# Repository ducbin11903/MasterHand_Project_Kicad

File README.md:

<h1 align="center">Motor Control Board</h1>

<p align="center" width="100%">
  
</p>

***

<p align="center">
  
&nbsp; &nbsp; &nbsp; &nbsp;
  
</p>

***

## SPECIFICATIONS

| Parameter | Value | 
| --- | --- |
| Dimensions | 79.0 × 65.81 mm |

***

## DIRECTORY STRUCTURE

    .
    ├─ Computations       # Misc calculations
    ├─ HTML               # HTML files for generated webpage
    ├─ Images             # Pictures and renders
    │
    ├─ kibot_resources    # External resources for KiBot
    │  ├─ colors          # Color theme for KiCad
    │  ├─ fonts           # Fonts used in the project
    │  ├─ scripts         # External scripts used with KiBot
    │  └─ templates       # Templates for KiBot generated reports
    │
    ├─ kibot_yaml         # KiBot YAML config files
    ├─ KiRI               # KiRI (PCB diff viewer) files
    │
    ├─ lib                # KiCad footprint and symbol libraries
    │  ├─ 3d_models       # Component 3D models
    │  ├─ lib_fp          # Footprint libraries
    │  └─ lib_sym         # Symbol libraries
    │
    ├─ Logos              # Logos
    │
    ├─ Manufacturing      # Assembly and fabrication documents
    │  ├─ Assembly        # Assembly documents (BoM, pos, notes)
    │  │
    │  └─ Fabrication     # Fabrication documents (ZIP, notes)
    │     ├─ Drill Tables # CSV drill tables
    │     └─ Gerbers      # Gerbers
    │
    ├─ Report             # Reports for ERC/DRC
    ├─ Schematic          # PDF of schematic
    ├─ Templates          # Title block templates
    ├─ Testing
    │  └─ Testpoints      # Testpoints tables      
    │
    └─ Variants           # Outputs for assembly variants

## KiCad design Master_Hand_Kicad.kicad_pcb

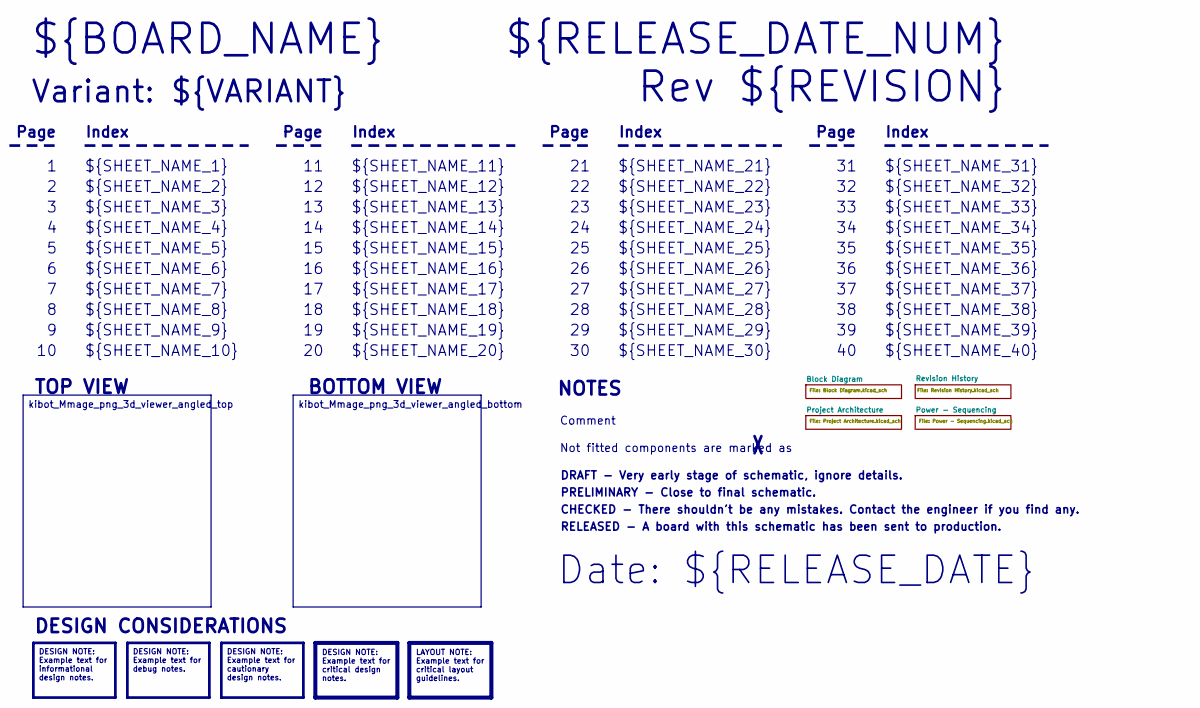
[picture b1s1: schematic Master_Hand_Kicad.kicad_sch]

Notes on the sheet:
Variant: ${VARIANT}
RELEASED - A board with this schematic has been sent to production.
${SHEET_NAME_24}
Index
Page
PRELIMINARY - Close to final schematic.
${SHEET_NAME_22}
DRAFT - Very early stage of schematic, ignore details.
${SHEET_NAME_12}
${SHEET_NAME_8}
${SHEET_NAME_2}
${SHEET_NAME_5}
${SHEET_NAME_20}
${SHEET_NAME_23}
${RELEASE_DATE_NUM}
${SHEET_NAME_35}
Not fitted components are marked as
${SHEET_NAME_11}
${SHEET_NAME_6}
${SHEET_NAME_37}
${SHEET_NAME_26}
${SHEET_NAME_36}
Rev ${REVISION}
${SHEET_NAME_15}
CHECKED - There shouldn't be any mistakes. Contact the engineer if you find any.
BOTTOM VIEW
${SHEET_NAME_14}
${SHEET_NAME_21}
${SHEET_NAME_17}
${SHEET_NAME_18}
Date: ${RELEASE_DATE}
${SHEET_NAME_7}
${SHEET_NAME_31}
${BOARD_NAME}
NOTES
${SHEET_NAME_40}
${SHEET_NAME_39}
${SHEET_NAME_32}
${SHEET_NAME_1}
${SHEET_NAME_9}

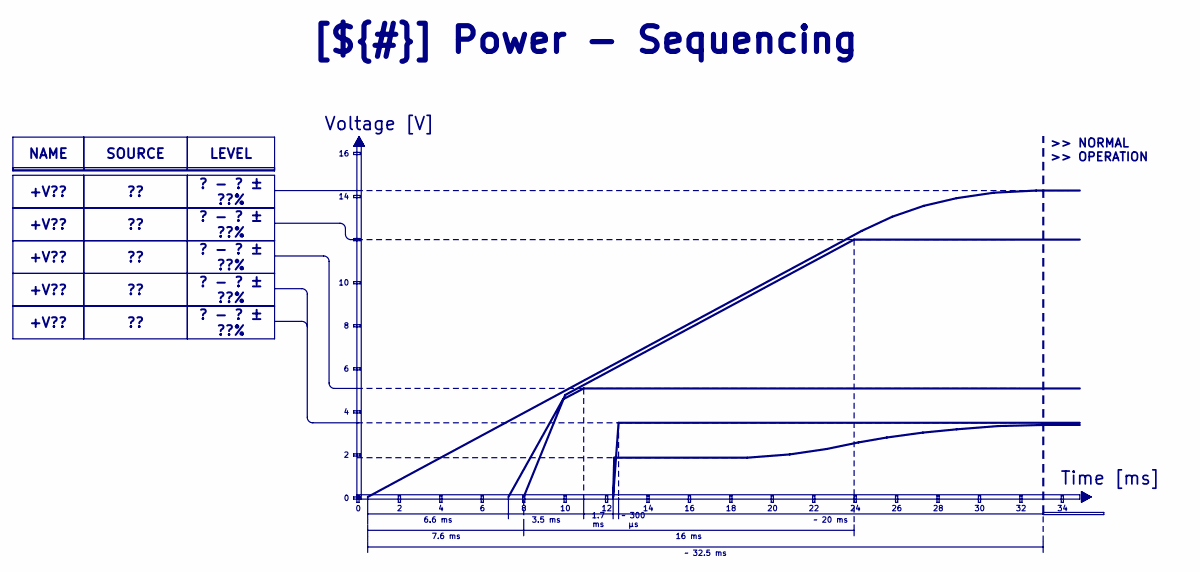
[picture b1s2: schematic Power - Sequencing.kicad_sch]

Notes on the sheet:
Voltage [V]
>> NORMAL >> OPERATION
Time [ms]
3.5 ms
7.6 ms
? - ? ± ??%
~ 300 μs
1.7 ms
16 ms
+V??
LEVEL
NAME
~ 20 ms
SOURCE
[${#}] ${TITLE}
6.6 ms
~ 32.5 ms

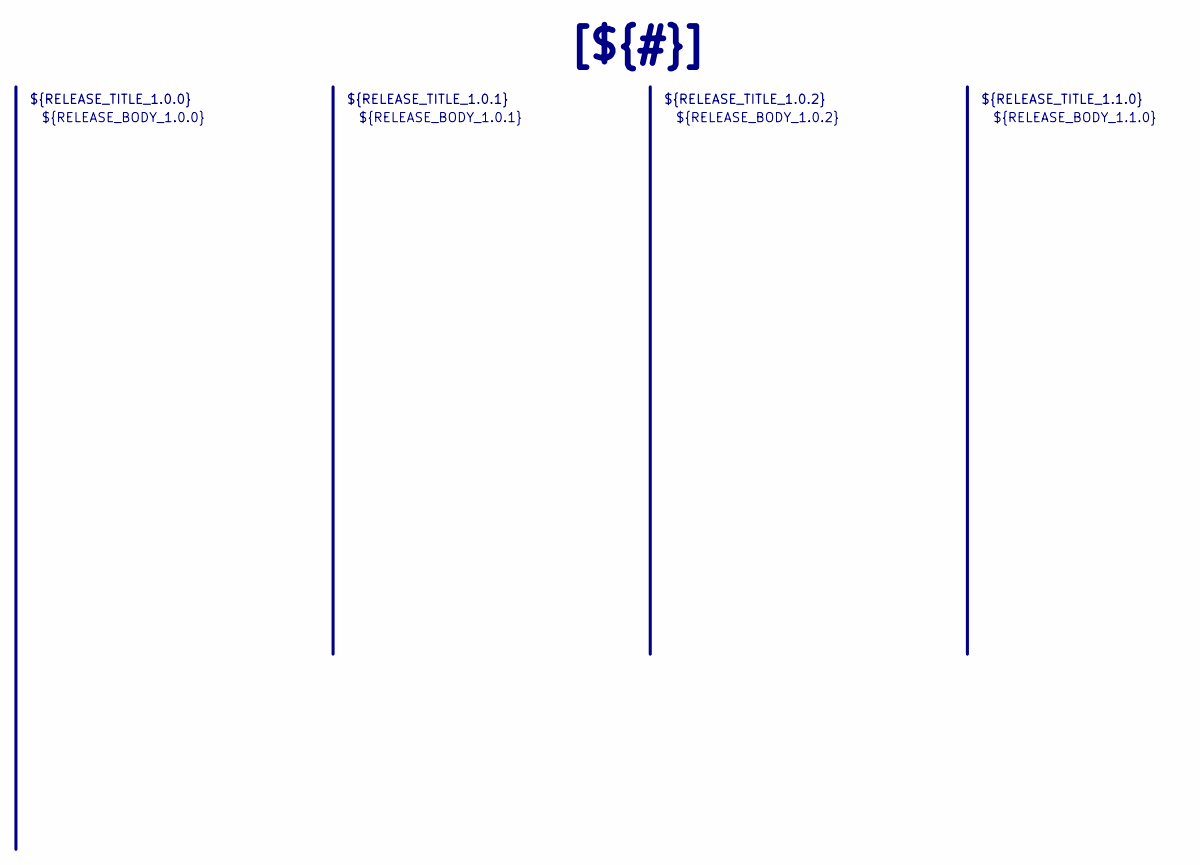
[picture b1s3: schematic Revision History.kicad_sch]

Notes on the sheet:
${RELEASE_BODY_1.1.0}
[${#}] ${TITLE}
${RELEASE_BODY_1.0.0}
${RELEASE_TITLE_1.0.2}
${RELEASE_BODY_1.0.2}
${RELEASE_BODY_1.0.1}
${RELEASE_TITLE_1.0.0}
${RELEASE_TITLE_1.0.1}
${RELEASE_TITLE_1.1.0}

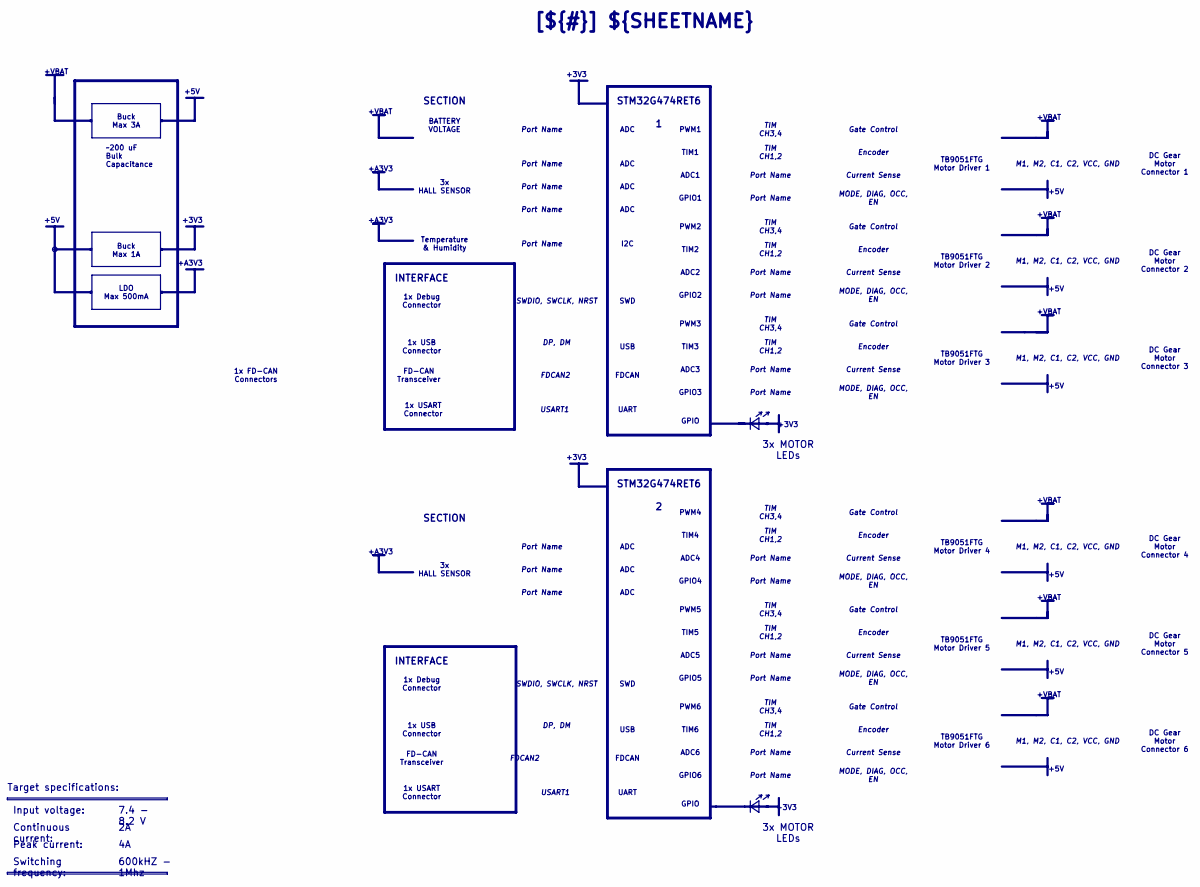
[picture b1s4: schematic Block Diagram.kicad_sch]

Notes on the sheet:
+5V
+A3V3
+VBAT
+3V3
+3V3
+VBAT
SWDIO, SWCLK, NRST
TIM CH3,4
I2C
MODE, DIAG, OCC, EN
Current Sense
TB9051FTG Motor Driver 6
7.4 - 8.2 V
TIM CH1,2
USB
ADC
M1, M2, C1, C2, VCC, GND
Temperature & Humidity
TIM6
1x FD-CAN Connectors
1x USART Connector
TIM CH3,4
600kHZ - 1Mhz
Port Name
STM32G474RET6
GPIO5
TIM1
TIM2
Gate Control
INTERFACE
SWD
DC Gear Motor Connector 3
3x HALL SENSOR
DC Gear Motor Connector 2
Peak current:
FDCAN
Encoder
PWM3
USART1
TB9051FTG Motor Driver 2

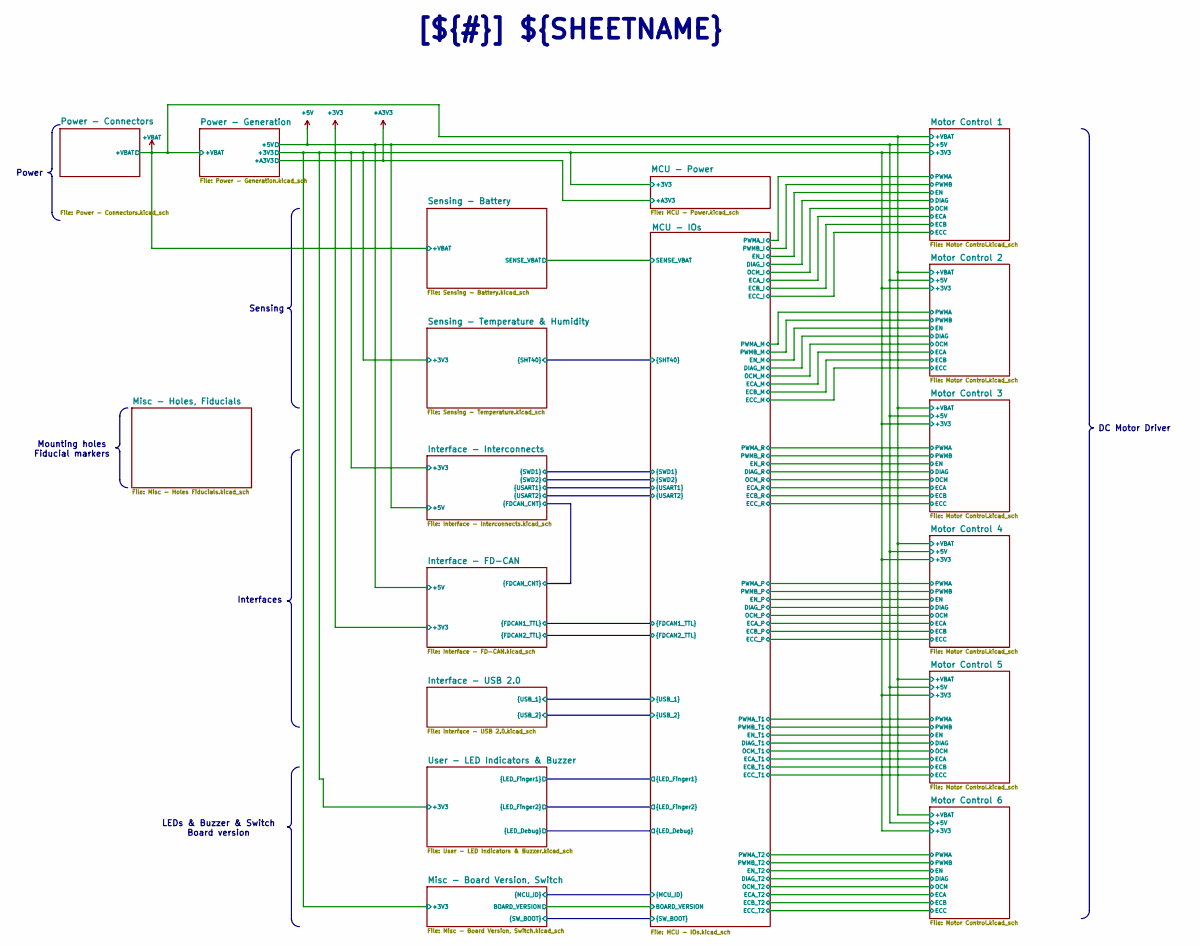
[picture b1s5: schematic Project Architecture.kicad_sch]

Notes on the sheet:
Mounting holes Fiducial markers
Interfaces
Power
LEDs & Buzzer & Switch Board version
[${#}] ${SHEETNAME}
Sensing
DC Motor Driver

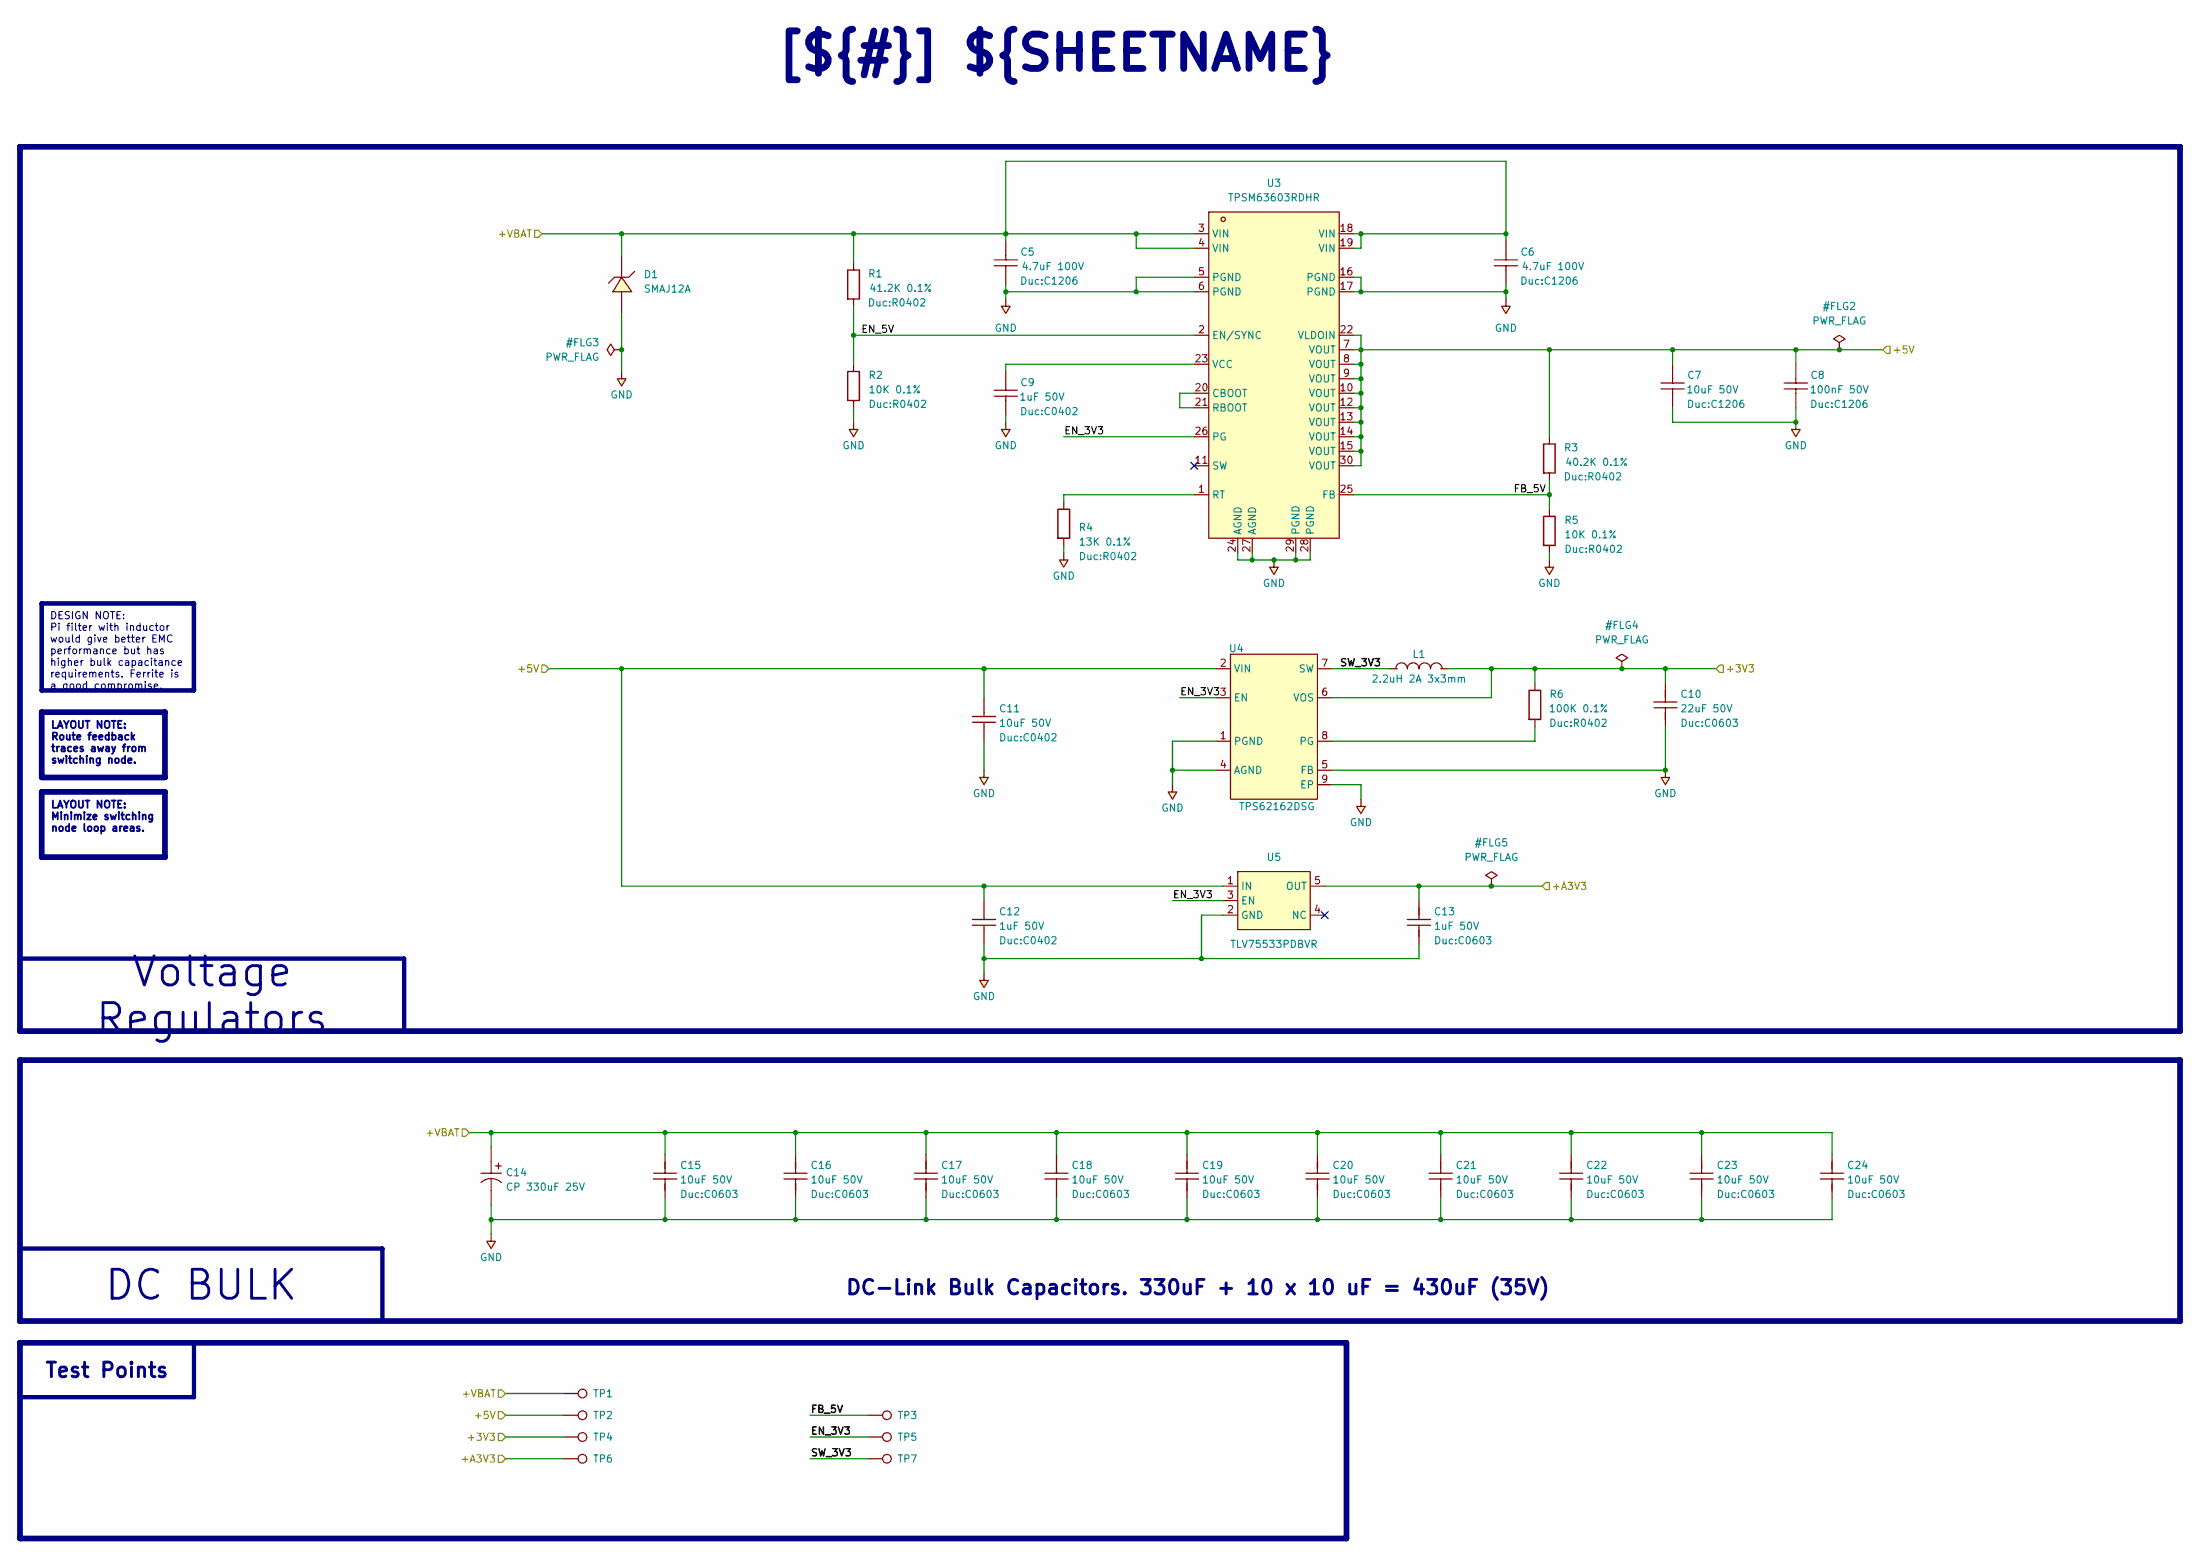
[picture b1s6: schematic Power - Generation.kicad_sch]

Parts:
C5, C6: 4.7uF 100V; C1206; MPN CC1206KKX7R9BB475; LCSC Part C132170
C7: 10uF 50V; C1206; MPN CC1206KKX7R9BB475; LCSC Part C132170
C8: 100nF 50V; C1206; MPN CC1206KKX7R9BB475; LCSC Part C132170
C9, C12: 1uF 50V; C0402; MPN CC0402KRX5R7BB105; LCSC Part C325464
C10: 22uF 50V; C0603; MPN CAP CER 0603; LCSC Part C14663
C11: 10uF 50V; C0402; MPN CC0402KRX5R7BB105; LCSC Part C325464
C13: 1uF 50V; C0603; MPN CAP CER 0603; LCSC Part C14663
C14: SM337M025E0800; CAP-SMD_BD6.3-L6.6-W6.6-FD-1; MPN SM337M025E0800; LCSC Part C44606382
C15, C16, C17, C18, C19, C20, C21, C22, C23, C24: 10uF 50V; C0603; MPN CAP CER 0603; LCSC Part C14663
D1: SMAJ12A; SMA_L4.3-W2.6-LS5.2-RD; MPN SMAJ12A; LCSC Part C148213
L1: ANR3015T2R2M; IND-SMD_L3.0-W3.0_SMNR3015; MPN ANR3015T2R2M; LCSC Part C6364793
R1: 41.2K 0.1%; R0402; MPN RT0402FRE07100KL; LCSC Part C728576
R2, R5: 10K 0.1%; R0402; MPN RT0402FRE07100KL; LCSC Part C728576
R3: 40.2K 0.1%; R0402; MPN RT0402FRE07100KL; LCSC Part C728576
R4: 13K 0.1%; R0402; MPN RT0402FRE07100KL; LCSC Part C728576
R6: 100K 0.1%; R0402; MPN RT0402FRE07100KL; LCSC Part C728576
TP1, TP2, TP3, TP4, TP5, TP6, TP7: TestPoint_Pad_D0.5mm
U3: TPSM63603RDHR; QFN-30_L6.0-W4.0-P0.50_TLVM13630RDHR; MPN TPSM63603RDHR; LCSC Part C5219327
U4: TPS62162DSG; WSON-8_L2.0-W2.0-P0.50-TL-EP; MPN TPS62162DSGR; LCSC Part C40256
U5: TLV75533PDBVR; SOT-23-5_L3.0-W1.7-P0.95-LS2.8-BR; MPN TLV75533PDBVR; LCSC Part C404027

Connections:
+3V3: C10.2, L1.2, R6.2, TP4.1, U4.6 (VOS); also elsewhere on the board
+5V: C7.2, C8.2, C11.2, C12.2, R3.2, TP2.1, U3.7 (VOUT), U3.8 (VOUT), U3.9 (VOUT), U3.10 (VOUT), U3.12 (VOUT), U3.13 (VOUT), U3.14 (VOUT), U3.15 (VOUT), U3.22 (VLDOIN), U3.30 (VOUT), U4.2 (VIN), U5.1 (IN); also elsewhere on the board
+A3V3: C13.2, TP6.1, U5.5 (OUT); also elsewhere on the board
+VBAT: C5.1, C6.2, C14.1, C15.1, C16.1, C17.1, C18.1, C19.1, C20.1, C21.1, C22.1, C23.1, C24.1, D1.1 (C), R1.2, TP1.1, U3.3 (VIN), U3.4 (VIN), U3.18 (VIN), U3.19 (VIN); also elsewhere on the board
/Project Architecture/Power - Generation/EN_3V3: TP5.1, U3.26 (PG), U4.3 (EN), U5.3 (EN)
/Project Architecture/Power - Generation/EN_5V: R1.1, R2.2, U3.2 (EN/SYNC)
/Project Architecture/Power - Generation/FB_5V: R3.1, R5.2, TP3.1, U3.25 (FB)
/Project Architecture/Power - Generation/SW_3V3: L1.1, TP7.1, U4.7 (SW)
GND: C5.2, C6.1, C7.1, C8.1, C9.2, C10.1, C11.1, C12.1, C13.1, C14.2, C15.2, C16.2, C17.2, C18.2, C19.2, C20.2, C21.2, C22.2, C23.2, C24.2, D1.2 (A), R2.1, R4.1, R5.1, U3.5 (PGND), U3.6 (PGND), U3.16 (PGND), U3.17 (PGND), U3.24 (AGND), U3.27 (AGND), U3.28 (PGND), U3.29 (PGND), U4.1 (PGND), U4.4 (AGND), U4.5 (FB), U4.9 (EP), U5.2 (GND); also elsewhere on the board
unnamed: U3.20 (CBOOT), U3.21 (RBOOT)
unnamed: R4.2, U3.1 (RT)
unnamed: C9.1, U3.23 (VCC)
unnamed: R6.1, U4.8 (PG)

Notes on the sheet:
DC BULK
Voltage Regulators
[${#}] ${SHEETNAME}
LAYOUT NOTE: Minimize switching node loop areas.
DESIGN NOTE: Pi filter with inductor would give better EMC performance but has higher bulk capacitance requirements. Ferrite is a good compromise.
DC-Link Bulk Capacitors. 330uF + 10 x 10 uF = 430uF (35V)
LAYOUT NOTE: Route feedback traces away from switching node.
Test Points

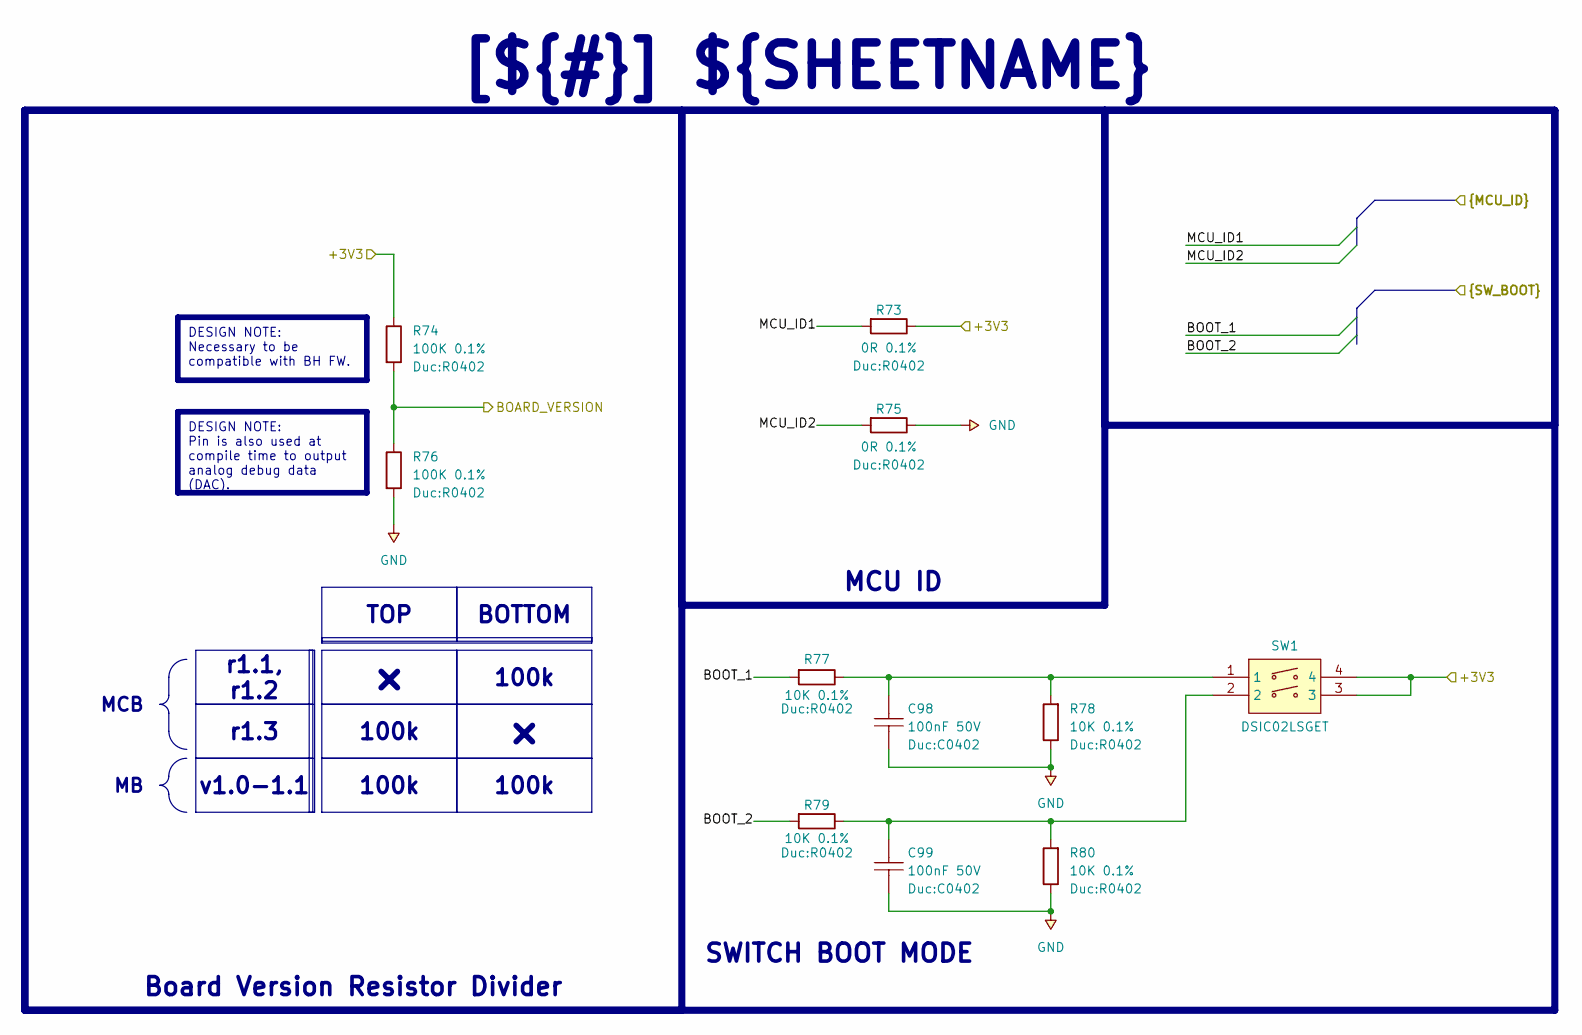
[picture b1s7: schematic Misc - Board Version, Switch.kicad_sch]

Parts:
C98, C99: 100nF 50V; C0402; MPN CC0402KRX5R7BB105; LCSC Part C325464
R73, R75: 0R 0.1%; R0402; MPN RT0402FRE07100KL; LCSC Part C728576
R74, R76: 100K 0.1%; R0402; MPN RT0402FRE07100KL; LCSC Part C728576
R77, R78, R79, R80: 10K 0.1%; R0402; MPN RT0402FRE07100KL; LCSC Part C728576
SW1: DSIC02LSGET; SW-SMD_DSIC02LSGET; MPN DSIC02LSGET; LCSC Part C3293152

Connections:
+3V3: R73.2, R74.2, SW1.3, SW1.4; also elsewhere on the board
/Project Architecture/MCU - IOs/BOARD_VERSION: R74.1, R76.2; also elsewhere on the board
/Project Architecture/MCU - IOs/BOOT_1: R77.1; also elsewhere on the board
/Project Architecture/MCU - IOs/BOOT_2: R79.1; also elsewhere on the board
/Project Architecture/MCU - IOs/MCU_ID1: R73.1; also elsewhere on the board
/Project Architecture/MCU - IOs/MCU_ID2: R75.1; also elsewhere on the board
GND: C98.1, C99.1, R75.2, R76.1, R78.2, R80.2; also elsewhere on the board
unnamed: C98.2, R77.2, R78.1, SW1.1
unnamed: C99.2, R79.2, R80.1, SW1.2

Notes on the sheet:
DESIGN NOTE: Necessary to be compatible with BH FW.
r1.3
MCU ID
TOP
BOTTOM
r1.1, r1.2
DESIGN NOTE: Pin is also used at compile time to output analog debug data (DAC).
Board Version Resistor Divider
100k
MCB
SWITCH BOOT MODE
[${#}] ${SHEETNAME}
v1.0-1.1

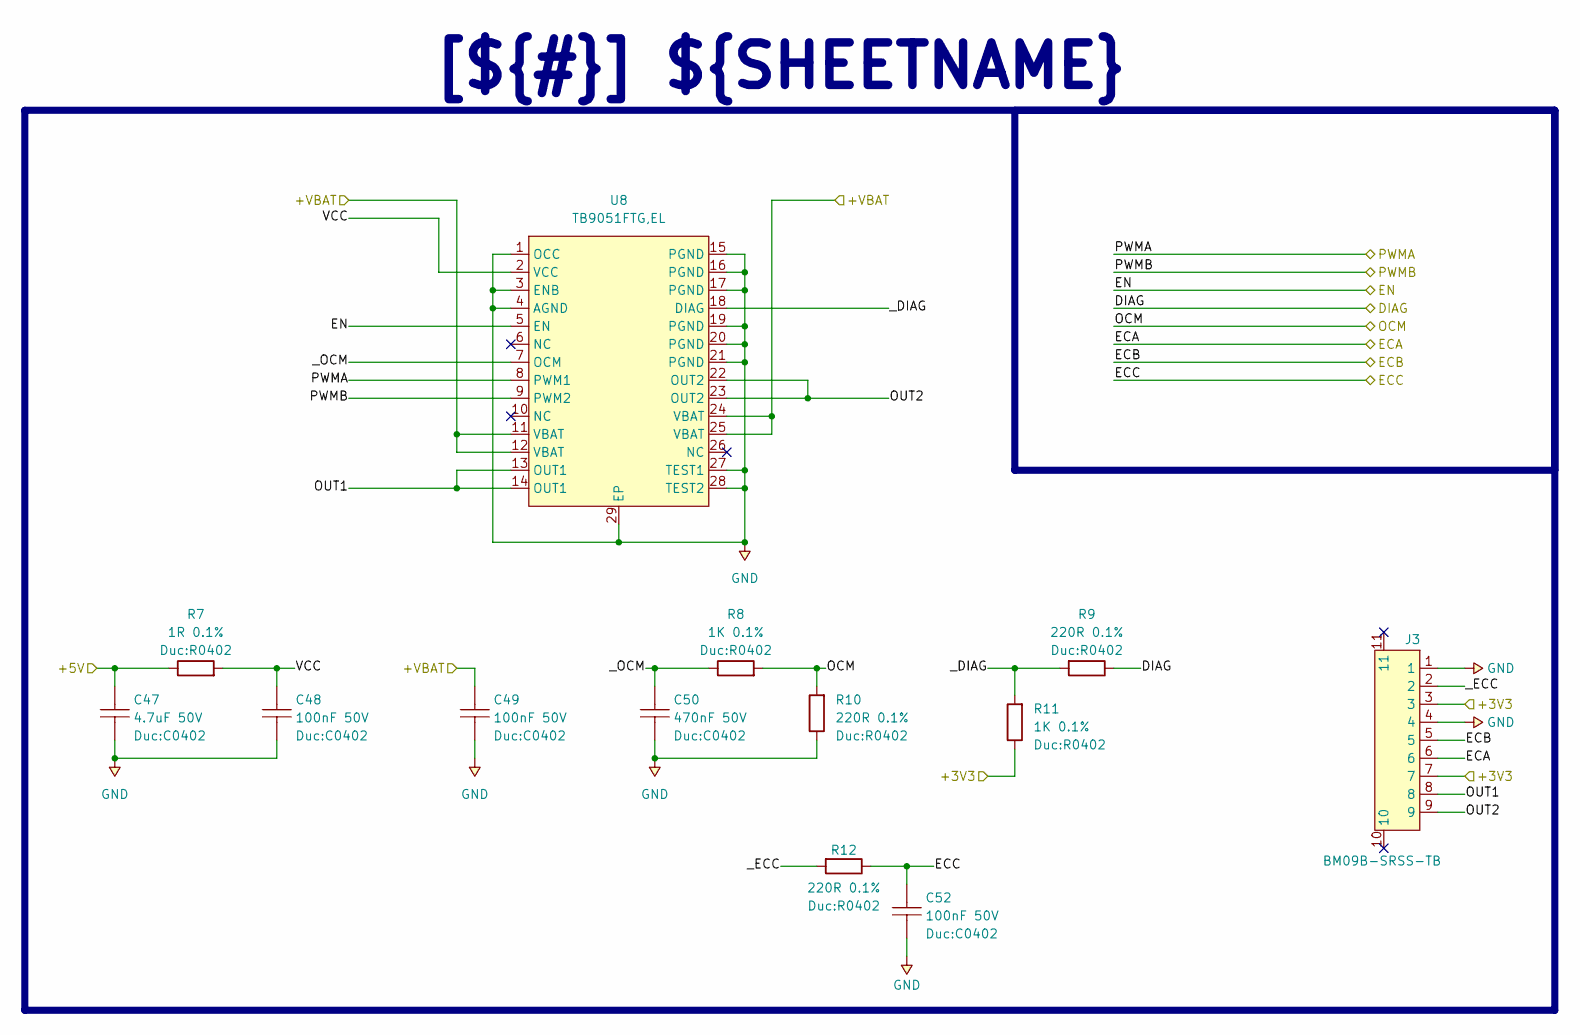
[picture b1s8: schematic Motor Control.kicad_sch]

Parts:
C47: 4.7uF 50V; C0402; MPN CC0402KRX5R7BB105; LCSC Part C325464
C48, C49, C52: 100nF 50V; C0402; MPN CC0402KRX5R7BB105; LCSC Part C325464
C50: 470nF 50V; C0402; MPN CC0402KRX5R7BB105; LCSC Part C325464
J3: BM09B-SRSS-TB; CONN-SMD_9P-P1.00_BM09B-SRSS-TB; MPN BM09B-SRSS-TB(LF)(SN); LCSC Part C160395
R7: 1R 0.1%; R0402; MPN RT0402FRE07100KL; LCSC Part C728576
R8, R11: 1K 0.1%; R0402; MPN RT0402FRE07100KL; LCSC Part C728576
R9, R10, R12: 220R 0.1%; R0402; MPN RT0402FRE07100KL; LCSC Part C728576
U8: TB9051FTG,EL; UQFN-28_L6.0-W6.0-P0.65-BL-EP4.0; MPN TB9051FTG,EL; LCSC Part C2150635

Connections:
+3V3: J3.3, J3.7, R11.2; also elsewhere on the board
+5V: C47.2, R7.2; also elsewhere on the board
+VBAT: C49.2, U8.11 (VBAT), U8.12 (VBAT), U8.24 (VBAT), U8.25 (VBAT); also elsewhere on the board
/Project Architecture/MCU - IOs/DIAG_I: R9.2; also elsewhere on the board
/Project Architecture/MCU - IOs/ECA_I: J3.6; also elsewhere on the board
/Project Architecture/MCU - IOs/ECB_I: J3.5; also elsewhere on the board
/Project Architecture/MCU - IOs/ECC_I: C52.2, R12.2; also elsewhere on the board
/Project Architecture/MCU - IOs/EN_I: U8.5 (EN); also elsewhere on the board
/Project Architecture/MCU - IOs/OCM_I: R8.1, R10.1; also elsewhere on the board
/Project Architecture/MCU - IOs/PWMA_I: U8.8 (PWM1); also elsewhere on the board
/Project Architecture/MCU - IOs/PWMB_I: U8.9 (PWM2); also elsewhere on the board
/Project Architecture/Motor Control 1/OUT1: J3.8, U8.13 (OUT1), U8.14 (OUT1)
/Project Architecture/Motor Control 1/OUT2: J3.9, U8.22 (OUT2), U8.23 (OUT2)
/Project Architecture/Motor Control 1/VCC: C48.2, R7.1, U8.2 (VCC)
/Project Architecture/Motor Control 1/_DIAG: R9.1, R11.1, U8.18 (DIAG)
/Project Architecture/Motor Control 1/_ECC: J3.2, R12.1
/Project Architecture/Motor Control 1/_OCM: C50.2, R8.2, U8.7 (OCM)
GND: C47.1, C48.1, C49.1, C50.1, C52.1, J3.1, J3.4, R10.2, U8.1 (OCC), U8.3 (ENB), U8.4 (AGND), U8.15 (PGND), U8.16 (PGND), U8.17 (PGND), U8.19 (PGND), U8.20 (PGND), U8.21 (PGND), U8.27 (TEST1), U8.28 (TEST2), U8.29 (EP); also elsewhere on the board

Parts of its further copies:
C53, C59, C65, C71, C77: 4.7uF 50V; C0402; MPN CC0402KRX5R7BB105; LCSC Part C325464
C54, C55, C58, C60, C61, C64, C66, C67, C70, C72, C73, C76, C78, C79, C82: 100nF 50V; C0402; MPN CC0402KRX5R7BB105; LCSC Part C325464
C56, C62, C68, C74, C80: 470nF 50V; C0402; MPN CC0402KRX5R7BB105; LCSC Part C325464
J4, J5, J6, J7, J8: BM09B-SRSS-TB; CONN-SMD_9P-P1.00_BM09B-SRSS-TB; MPN BM09B-SRSS-TB(LF)(SN); LCSC Part C160395
R13, R19, R25, R31, R37: 1R 0.1%; R0402; MPN RT0402FRE07100KL; LCSC Part C728576
R14, R17, R20, R23, R26, R29, R32, R35, R38, R41: 1K 0.1%; R0402; MPN RT0402FRE07100KL; LCSC Part C728576
R15, R16, R18, R21, R22, R24, R27, R28, R30, R33, R34, R36, R39, R40, R42: 220R 0.1%; R0402; MPN RT0402FRE07100KL; LCSC Part C728576
U9, U10, U11, U12, U13: TB9051FTG,EL; UQFN-28_L6.0-W6.0-P0.65-BL-EP4.0; MPN TB9051FTG,EL; LCSC Part C2150635

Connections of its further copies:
+3V3: J4.3, J4.7, J5.3, J5.7, J6.3, J6.7, J7.3, J7.7, J8.3, J8.7, R17.2, R23.2, R29.2, R35.2, R41.2; also elsewhere on the board
+5V: C53.2, C59.2, C65.2, C71.2, C77.2, R13.2, R19.2, R25.2, R31.2, R37.2; also elsewhere on the board
+VBAT: C55.2, C61.2, C67.2, C73.2, C79.2, U9.11 (VBAT), U9.12 (VBAT), U9.24 (VBAT), U9.25 (VBAT), U10.11 (VBAT), U10.12 (VBAT), U10.24 (VBAT), U10.25 (VBAT), U11.11 (VBAT), U11.12 (VBAT), U11.24 (VBAT), U11.25 (VBAT), U12.11 (VBAT), U12.12 (VBAT), U12.24 (VBAT), U12.25 (VBAT), U13.11 (VBAT), U13.12 (VBAT), U13.24 (VBAT), U13.25 (VBAT); also elsewhere on the board
/Project Architecture/MCU - IOs/DIAG_M: R15.2; also elsewhere on the board
/Project Architecture/MCU - IOs/DIAG_P: R27.2; also elsewhere on the board
/Project Architecture/MCU - IOs/DIAG_R: R21.2; also elsewhere on the board
/Project Architecture/MCU - IOs/DIAG_T1: R33.2; also elsewhere on the board
/Project Architecture/MCU - IOs/DIAG_T2: R39.2; also elsewhere on the board
/Project Architecture/MCU - IOs/ECA_M: J4.6; also elsewhere on the board
/Project Architecture/MCU - IOs/ECA_P: J6.6; also elsewhere on the board
/Project Architecture/MCU - IOs/ECA_R: J5.6; also elsewhere on the board
/Project Architecture/MCU - IOs/ECA_T1: J7.6; also elsewhere on the board
/Project Architecture/MCU - IOs/ECA_T2: J8.6; also elsewhere on the board
/Project Architecture/MCU - IOs/ECB_M: J4.5; also elsewhere on the board
/Project Architecture/MCU - IOs/ECB_P: J6.5; also elsewhere on the board
/Project Architecture/MCU - IOs/ECB_R: J5.5; also elsewhere on the board
/Project Architecture/MCU - IOs/ECB_T1: J7.5; also elsewhere on the board
/Project Architecture/MCU - IOs/ECB_T2: J8.5; also elsewhere on the board
/Project Architecture/MCU - IOs/ECC_M: C58.2, R18.2; also elsewhere on the board
/Project Architecture/MCU - IOs/ECC_P: C70.2, R30.2; also elsewhere on the board
/Project Architecture/MCU - IOs/ECC_R: C64.2, R24.2; also elsewhere on the board
/Project Architecture/MCU - IOs/ECC_T1: C76.2, R36.2; also elsewhere on the board
/Project Architecture/MCU - IOs/ECC_T2: C82.2, R42.2; also elsewhere on the board
/Project Architecture/MCU - IOs/EN_M: U9.5 (EN); also elsewhere on the board
/Project Architecture/MCU - IOs/EN_P: U11.5 (EN); also elsewhere on the board
/Project Architecture/MCU - IOs/EN_R: U10.5 (EN); also elsewhere on the board
/Project Architecture/MCU - IOs/EN_T1: U12.5 (EN); also elsewhere on the board
/Project Architecture/MCU - IOs/EN_T2: U13.5 (EN); also elsewhere on the board
/Project Architecture/MCU - IOs/OCM_M: R14.1, R16.1; also elsewhere on the board
/Project Architecture/MCU - IOs/OCM_P: R26.1, R28.1; also elsewhere on the board
/Project Architecture/MCU - IOs/OCM_R: R20.1, R22.1; also elsewhere on the board
/Project Architecture/MCU - IOs/OCM_T1: R32.1, R34.1; also elsewhere on the board
/Project Architecture/MCU - IOs/OCM_T2: R38.1, R40.1; also elsewhere on the board
/Project Architecture/MCU - IOs/PWMA_M: U9.8 (PWM1); also elsewhere on the board
/Project Architecture/MCU - IOs/PWMA_P: U11.8 (PWM1); also elsewhere on the board
/Project Architecture/MCU - IOs/PWMA_R: U10.8 (PWM1); also elsewhere on the board
/Project Architecture/MCU - IOs/PWMA_T1: U12.8 (PWM1); also elsewhere on the board
/Project Architecture/MCU - IOs/PWMA_T2: U13.8 (PWM1); also elsewhere on the board
/Project Architecture/MCU - IOs/PWMB_M: U9.9 (PWM2); also elsewhere on the board
/Project Architecture/MCU - IOs/PWMB_P: U11.9 (PWM2); also elsewhere on the board
/Project Architecture/MCU - IOs/PWMB_R: U10.9 (PWM2); also elsewhere on the board
/Project Architecture/MCU - IOs/PWMB_T1: U12.9 (PWM2); also elsewhere on the board
/Project Architecture/MCU - IOs/PWMB_T2: U13.9 (PWM2); also elsewhere on the board
/Project Architecture/Motor Control 2/OUT1: J4.8, U9.13 (OUT1), U9.14 (OUT1)
/Project Architecture/Motor Control 2/OUT2: J4.9, U9.22 (OUT2), U9.23 (OUT2)
/Project Architecture/Motor Control 2/VCC: C54.2, R13.1, U9.2 (VCC)
/Project Architecture/Motor Control 2/_DIAG: R15.1, R17.1, U9.18 (DIAG)
/Project Architecture/Motor Control 2/_ECC: J4.2, R18.1
/Project Architecture/Motor Control 2/_OCM: C56.2, R14.2, U9.7 (OCM)
/Project Architecture/Motor Control 3/OUT1: J5.8, U10.13 (OUT1), U10.14 (OUT1)
/Project Architecture/Motor Control 3/OUT2: J5.9, U10.22 (OUT2), U10.23 (OUT2)
/Project Architecture/Motor Control 3/VCC: C60.2, R19.1, U10.2 (VCC)
/Project Architecture/Motor Control 3/_DIAG: R21.1, R23.1, U10.18 (DIAG)
/Project Architecture/Motor Control 3/_ECC: J5.2, R24.1
/Project Architecture/Motor Control 3/_OCM: C62.2, R20.2, U10.7 (OCM)
/Project Architecture/Motor Control 4/OUT1: J6.8, U11.13 (OUT1), U11.14 (OUT1)
/Project Architecture/Motor Control 4/OUT2: J6.9, U11.22 (OUT2), U11.23 (OUT2)
/Project Architecture/Motor Control 4/VCC: C66.2, R25.1, U11.2 (VCC)
/Project Architecture/Motor Control 4/_DIAG: R27.1, R29.1, U11.18 (DIAG)
/Project Architecture/Motor Control 4/_ECC: J6.2, R30.1
/Project Architecture/Motor Control 4/_OCM: C68.2, R26.2, U11.7 (OCM)
/Project Architecture/Motor Control 5/OUT1: J7.8, U12.13 (OUT1), U12.14 (OUT1)
/Project Architecture/Motor Control 5/OUT2: J7.9, U12.22 (OUT2), U12.23 (OUT2)
/Project Architecture/Motor Control 5/VCC: C72.2, R31.1, U12.2 (VCC)
/Project Architecture/Motor Control 5/_DIAG: R33.1, R35.1, U12.18 (DIAG)
/Project Architecture/Motor Control 5/_ECC: J7.2, R36.1
/Project Architecture/Motor Control 5/_OCM: C74.2, R32.2, U12.7 (OCM)
/Project Architecture/Motor Control 6/OUT1: J8.8, U13.13 (OUT1), U13.14 (OUT1)
/Project Architecture/Motor Control 6/OUT2: J8.9, U13.22 (OUT2), U13.23 (OUT2)
/Project Architecture/Motor Control 6/VCC: C78.2, R37.1, U13.2 (VCC)
/Project Architecture/Motor Control 6/_DIAG: R39.1, R41.1, U13.18 (DIAG)
/Project Architecture/Motor Control 6/_ECC: J8.2, R42.1
/Project Architecture/Motor Control 6/_OCM: C80.2, R38.2, U13.7 (OCM)
GND: C53.1, C54.1, C55.1, C56.1, C58.1, C59.1, C60.1, C61.1, C62.1, C64.1, C65.1, C66.1, C67.1, C68.1, C70.1, C71.1, C72.1, C73.1, C74.1, C76.1, C77.1, C78.1, C79.1, C80.1, C82.1, J4.1, J4.4, J5.1, J5.4, J6.1, J6.4, J7.1, J7.4, J8.1, J8.4, R16.2, R22.2, R28.2, R34.2, R40.2, U9.1 (OCC), U9.3 (ENB), U9.4 (AGND), U9.15 (PGND), U9.16 (PGND), U9.17 (PGND), U9.19 (PGND), U9.20 (PGND), U9.21 (PGND), U9.27 (TEST1), U9.28 (TEST2), U9.29 (EP), U10.1 (OCC), U10.3 (ENB), U10.4 (AGND), U10.15 (PGND), U10.16 (PGND), U10.17 (PGND), U10.19 (PGND), U10.20 (PGND), U10.21 (PGND), U10.27 (TEST1), U10.28 (TEST2), U10.29 (EP), U11.1 (OCC), U11.3 (ENB), U11.4 (AGND), U11.15 (PGND), U11.16 (PGND), U11.17 (PGND), U11.19 (PGND), U11.20 (PGND), U11.21 (PGND), U11.27 (TEST1), U11.28 (TEST2), U11.29 (EP), U12.1 (OCC), U12.3 (ENB), U12.4 (AGND), U12.15 (PGND), U12.16 (PGND), U12.17 (PGND), U12.19 (PGND), U12.20 (PGND), U12.21 (PGND), U12.27 (TEST1), U12.28 (TEST2), U12.29 (EP), U13.1 (OCC), U13.3 (ENB), U13.4 (AGND), U13.15 (PGND), U13.16 (PGND), U13.17 (PGND), U13.19 (PGND), U13.20 (PGND), U13.21 (PGND), U13.27 (TEST1), U13.28 (TEST2), U13.29 (EP); also elsewhere on the board

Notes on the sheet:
[${#}] ${SHEETNAME}

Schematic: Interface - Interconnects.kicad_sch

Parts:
C91: 4.7uF 50V; C0603; MPN CAP CER 0603; LCSC Part C14663
D8: PESD1CAN; SOT-23-3_L2.9-W1.3-P1.90-LS2.4-BR; MPN PESD1CAN; LCSC Part C21713981
J11: 1.25-3PLTDK; CONN-SMD_3P-P1.25_SHOU_1.25-3PLTDK; MPN 1.25-3PLTDK; LCSC Part C3008548
J12: 5025982393; FPC-SMD_23P-P0.60_502598-2393; MPN 5025982393; LCSC Part C7021254
J13, J14: HCZZ0015-5; CONN-SMD_5P-P1.25_HCZZ0015-5; MPN HCZZ0015-5; LCSC Part C7433471
R57, R58: 60R4 0.1%; R0603; MPN RT0603FRE13100KL; LCSC Part C4107493

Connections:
+3V3: J13.1, J14.1; also elsewhere on the board
+5V: J12.2, J12.4, J12.6, J12.8, J12.10, J12.12, J12.14; also elsewhere on the board
/Project Architecture/Interface - FD-CAN/FDCAN_N: D8.1, J11.2, R58.1; also elsewhere on the board
/Project Architecture/Interface - FD-CAN/FDCAN_P: D8.2, J11.3, R57.2; also elsewhere on the board
/Project Architecture/Interface - Interconnects/NRST1: J14.4; also elsewhere on the board
/Project Architecture/Interface - Interconnects/NRST2: J13.4; also elsewhere on the board
/Project Architecture/Interface - Interconnects/SWCLK1: J14.2; also elsewhere on the board
/Project Architecture/Interface - Interconnects/SWCLK2: J13.2; also elsewhere on the board
/Project Architecture/Interface - Interconnects/SWDIO1: J14.3; also elsewhere on the board
/Project Architecture/Interface - Interconnects/SWDIO2: J13.3; also elsewhere on the board
/Project Architecture/Interface - Interconnects/USART1_CK1: J12.17; also elsewhere on the board
/Project Architecture/Interface - Interconnects/USART1_CK2: J12.9; also elsewhere on the board
/Project Architecture/Interface - Interconnects/USART1_RX1: J12.19; also elsewhere on the board
/Project Architecture/Interface - Interconnects/USART1_RX2: J12.13; also elsewhere on the board
/Project Architecture/Interface - Interconnects/USART1_TX1: J12.21; also elsewhere on the board
/Project Architecture/Interface - Interconnects/USART1_TX2: J12.11; also elsewhere on the board
GND: C91.2, D8.3, J11.1, J12.1, J12.3, J12.5, J12.7, J12.15, J12.16, J12.18, J12.20, J12.22, J12.23, J13.5, J14.5; also elsewhere on the board
unnamed: C91.1, R57.1, R58.2

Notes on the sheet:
Reset Button
SWD Debug Connector
FD-CAN Connector and Termination
[${#}] ${SHEETNAME}
FFC Connector MCB & MB
